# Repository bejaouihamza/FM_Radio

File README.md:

# 📻 FM Radio Receiver – Technical Overview

## 📑 Introduction
This project is a simple **FM radio receiver** built using analog components and an RF tuner stage.  
It demonstrates the **principles of frequency modulation** (FM) reception, the **electromagnetic theory**,  
and the **electronics** needed to detect and play broadcast FM audio.

---

## 📷 Schematic

---

## ⚡ How FM Radio Works
**FM (Frequency Modulation)** encodes audio into a radio wave by varying its **frequency**  
while keeping the **amplitude constant**.

### Electromagnetic Principle
- FM signals are **electromagnetic waves** traveling at the speed of light (*c = 3×10⁸ m/s*).
- A broadcast station transmits a **carrier frequency** in the **VHF band** (88–108 MHz).
- The antenna captures a small portion of this wave and converts it into a **weak AC signal**.
- The circuit processes this to recover the original **audio waveform**.

---

## 📐 The Math Behind FM
If the **carrier wave** is:

<p align="center">
c(t) = A<sub>c</sub> · cos( 2π f<sub>c</sub> t )
</p>

In FM, the **instantaneous frequency** varies with the audio signal *m(t)*:

<p align="center">
s(t) = A<sub>c</sub> · cos[ 2π f<sub>c</sub> t + β · sin( 2π f<sub>m</sub> t ) ]
</p>

Where:  
- *f<sub>m</sub>* = maximum frequency of the audio signal  
- β = modulation index = Δf / f<sub>m</sub>  
- Δf = frequency deviation (max shift from f<sub>c</sub>)

Typical broadcast values:  
- Δf ≈ 75 kHz  
- f<sub>m</sub> ≤ 15 kHz  

---

## 🔧 Circuit Overview
**1. Antenna & LC Tuner**  
Captures the FM signal and selects the desired frequency using:

<p align="center">
f<sub>res</sub> = 1 / ( 2π √(LC) )
</p>

**2. RF Amplifier**  
Boosts the weak signal without adding too much noise.

**3. Mixer & Local Oscillator**  
Shifts the RF signal to an **Intermediate Frequency (IF)** (10.7 MHz).

**4. IF Amplifier & Limiter**  
Amplifies and removes amplitude variations (FM carries info in frequency only).

**5. FM Demodulator**  
Converts frequency changes into voltage variations (audio signal).

**6. Audio Amplifier**  
Boosts the audio to drive a speaker.

---

## 📊 Signal Flow
```mermaid
graph LR
    A[Antenna] --> B[LC Tuned Circuit]
    B --> C[RF Amplifier]
    C --> D[Mixer]
    E[Local Oscillator] --> D
    D --> F[IF Filter]
    F --> G[IF Amplifier]
    G --> H[Limiter]
    H --> I[FM Discriminator]
    I --> J[Audio Amplifier]
    J --> K[Speaker]

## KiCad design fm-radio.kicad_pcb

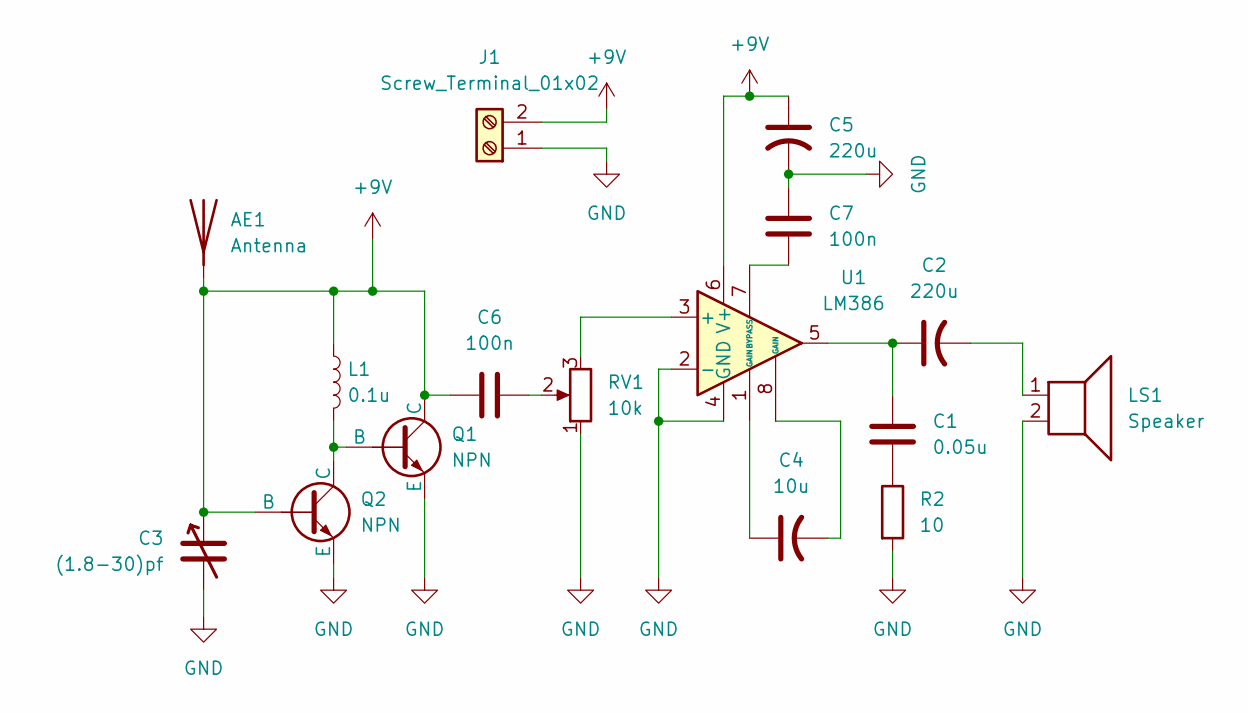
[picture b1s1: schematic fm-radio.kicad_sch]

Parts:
AE1: Antenna; NiceRF_SW868-TH13_868Mhz
C1: 0.05u; C_Disc_D3.0mm_W1.6mm_P2.50mm
C2, C5: 220u; CP_Radial_D5.0mm_P2.50mm
C3: (1.8-30)pf; C_Trimmer_Murata_TZB4-A
C4: 10u; CP_Radial_D5.0mm_P2.50mm
C6, C7: 100n; C_Disc_D3.0mm_W1.6mm_P2.50mm
J1: Screw_Terminal_01x02; TerminalBlock_Phoenix_MKDS-1,5-2-5.08_1x02_P5.08mm_Horizont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
L1: 0.1u; L_Axial_L11.0mm_D4.5mm_P15.24mm_Horizontal_Fastron_MECC
LS1: Speaker; SPKR_AST-1732MR-R
Q1, Q2: NPN; TO-92_Inline
R2: 10; R_Axial_DIN0207_L6.3mm_D2.5mm_P7.62mm_Horizontal
RV1: 10k; Potentiometer_Alps_RK09Y11_Single_Horizontal
U1: LM386; DIP-8_W7.62mm

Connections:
+9V: AE1.1 (A), C3.1, C5.1, C6.1, J1.2, L1.1, Q1.1 (C), Q2.2 (B), U1.6 (V+)
GND: C3.2, C5.2, C7.1, J1.1, LS1.2, Q1.3 (E), Q2.3 (E), R2.2, RV1.1, U1.2 (-), U1.4 (GND)
unnamed: C1.1, C2.1, U1.5
unnamed: C1.2, R2.1
unnamed: C2.2, LS1.1
unnamed: C4.1, U1.1 (GAIN)
unnamed: C4.2, U1.8 (GAIN)
unnamed: C6.2, RV1.2
unnamed: L1.2, Q1.2 (B), Q2.1 (C)
unnamed: RV1.3, U1.3 (+)
unnamed: C7.2, U1.7 (BYPASS)

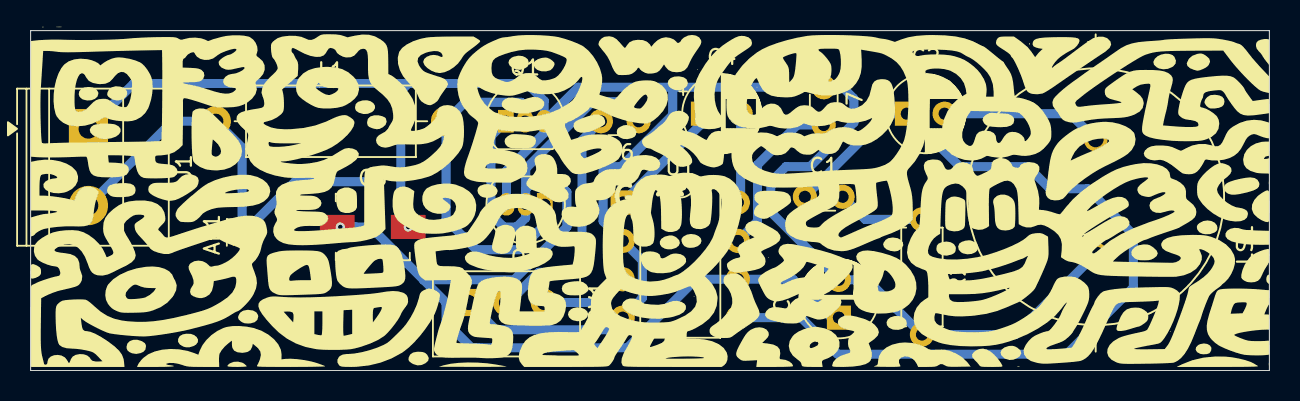
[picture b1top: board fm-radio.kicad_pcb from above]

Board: 2 copper layers, 82.0 x 22.5 mm, 16 parts (0 on the bottom side), 11 nets.
